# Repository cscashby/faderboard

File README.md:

# Fader Board (AKA Fraken-Mixer)

Multi-channel DAW control designed for portable wireless musical theatre use

## Problem statement

Normally musical theatre shows involve a fairly high number of radio microphones and a decent sized band/orchestra.  Generally in order to avoid feedback and other issues, the sound engineer needs to closely monitor / mix and quickly change faders during each scene to minimise the number of mics 'live' at any one time, and adjust for differences in the actors' voices and song dynamics.

In a traditional proscenium theatre this is fairly easy - a space is reserved at the back for the mix position, and the mixer and processing equipment (as well as the source for any SFX) is at the rear of the hall.

Enter promenade, or immersive, musical theatre - where the cast and audience are often in the same space, and the audience move through a number of rooms as the cast and the action takes them.

This is a very new genre of musical theatre, and hasn't really been done on a professional scale before - at least to my knowledge - and so when I was asked to do [Parade in Hemel Hempstead's Frogmore Paper Mill by Vivo D'Arte](http://www.vivodarte.co.uk/news.htm) - which required 20 radio microphones, a 7 piece orchestra, all in 5 different spaces, I apprehensively grasped at the challenge.

My approach at the time was to use a [Behringer Xtouch](https://www.musictri.be/Categories/Behringer/Computer-Audio/Desktop-Controllers/X-TOUCH/p/P0B1X) control surface, with a battery power unit and WiFi access client.  The result was good<sup>[1](#myfootnote1)</sup>, but it was a challenge because I only had 8 faders to use, couldn't change the 'page' or 'scene' myself, and couldn't trigger SFX or change speaker routing; I had a very capable team working with me who could do all of the above, so I managed, but it also was a very heavy box of tricks.

Another issue which arose over time was that the WiFi control was patchy - as the Xtouch isn't designed to be used with a spotty network connection, and being WiFi across a large space, the access client needed to disconnect and reconnect between multiple access points, disconnections were difficult - the Xtouch actually drops all the faders to -∞ so if you happen to touch them as it reconnects the channel dies unexpectedly. Not great.

So, what is required is a custom-built control surface which can control a number of channels of a mixing desk, without the constraints of a direct control solution like the Xtouch, and without the inherent problems with WiFi.

## Initial thoughts / concepts

### Scribble

Not very tidy, but hopefully this helps illustrate what's supposed to be happening.

### Tech decision

I went for an Arduino base for this project as I need embedded reliability and performance, without the overheads and inherent risks of using a SoC like the Raspberry Pi.  Given the complexity and number of I/O connections needed, I am basing the solution on an AT Mega 2560 - I got hold of [this dev board](http://amzn.to/2lO5UGc), but will probably design my own board from scratch for compactness

### Wireless comms

I need a long-range, full duplex transmit/receive solution for reasonably small payloads with a limited amount of overhead / latency.  I came across [LoRa](https://www.lora-alliance.org/) which seems to fit the bill, and I bought a couple of [dev boards for the RA-02 chip](http://amzn.to/2ELpx9M) which uses 433 MHz (or a couple of other free to use frequenceis).  I haven't completed testing yet but it seems to work well for my purposes.  What's more as it's designed for IoT, multiple receivers can be used to widen the transmit range if needed.

### Faders

Key to the solution is going to be the quality of fader units available, and they have to be motorised so they can be preset to values, and so that the sound #2s can also control if required.

Rather than evaluate a whole bunch of faders, I decided to buy [replacement faders for the Xtouch unit](https://www.gear4music.com/PA-DJ-and-Lighting/Behringer-X-Touch-Motor-Fader-MF100T-Set-of-5/1WME) instead - they are not that expensive, and I know them to be good.  They are 10 kΩ linear slide pots with a fast, accurate motor, and a touch sensitivity (capacitive touch) pin.

Touch sensitivity isn't something I've previously thought about, but this is a great option as it means that I can minimise my payload sent over the wire to only those faders which are being touched - making the device hopefully far more responsive.

### Scribble strips

Every good sound engineer deserves scribble strips (or something!) - they are invaluable for Musical Theatre - as each scene has different DCA assignments running, you can very quickly forget where you are as an operator.

I wanted multiple colours - as colour is a great way to distinguish between each channel.

I came across [these little OLED displays](https://thepihut.com/products/adafruit-monochrome-0-96-128x64-oled-graphic-display) which seem perfect as they're small, bright and easy to control via SPI.  I haven't yet received them so I'll update here as to how suitable they are.

Controlling lots of them isn't directly supported by their libraries so I'll need to do some custom coding to modify them for multiple units - multiplexing them through multiple CS pins.

### Everything else

I decided to duplicate the work I did in another project - '[pi-showcontrol'](github.com/cscashby/pi-showcontrol) and have a small TFT screen and programmable buttons in a 'master section' in the box - that way I can use SFX and have some feedback, possibly even plain text sent back to me by the Sound #2s which will hopefully be very useful.

### Power supply

This is probably the thing I've thought the least about.  I have a very reliable, high power battery which will give me any DC voltage I like and sensibly monitor time remaining, so I may stick with that for now; so a 5.5mm/2.5mm DC power jack may be all I need - probably 12v to minimise voltage regulator heating and run the whole thing at 5v.  However, if I feel brave later on I may well implement a battery control / charge unit.

### Physical manufacture

In my mind at present, I think the best approach is going to be to create a number of different PCBs:

1. Faders - in groups of 8 (so two identical boards).
2. Master control section - the TFT (although this may just be a module bolted to the case), buttons and big 'go' buttons).
3. Control board - the Arduino, radio chips and logic required to get the thing running.
4. Power supply - not sure what this will entail yet - watch this space.

I'd like to keep the unit as light as possible, but it will need sensible shielding (likely with pass-through capacitors for the 433 MHz antennae) - so I will be building the case out of sheet aluminium, probably cut using a CNC mill, or laser cut by a third party fabrication shop.  All of the controls will be mounted on the top panel, the control / power boards likely on the bottom panel, and the rear will be used for wired connections for charging, firmware upgrades and diagnostics.

On the sides of the box (which will likely need to be thicker / better reinforced) I will have holes for the straps which I will wear to use the unit whilst walking around (in [ice cream tray style](http://www.promotional-images.co.uk/ProdImages/2f9f440d-2c25-4093-97b0-d831b5edaa2b/classic2-lg.jpg) without the ice creams)

### The other end

Again this is early stages of the thought process, but a LoRa chip (probably the development board itself) with an ethernet HAT, which delivers an OSC payload to the mixing desk or a mac running [qLab](http://www.figure53.com/qlab).  Some form of queuing will be required so that if I end up with more than one of the receivers, then a controller will be required to marshal, deduplicate and send on this queue.

## Footnotes

<a name="myfootnote1">1</a>: 'No sitting at the back for him – [cscashby] he too followed the audience around with his sound desk in an usherette’s tray, ensuring that every cast member was heard, no matter what part of the building they were in.' [from Musical Theatre Review](http://musicaltheatrereview.com/parade-frogmore-paper-mill-hemel-hempstead/)

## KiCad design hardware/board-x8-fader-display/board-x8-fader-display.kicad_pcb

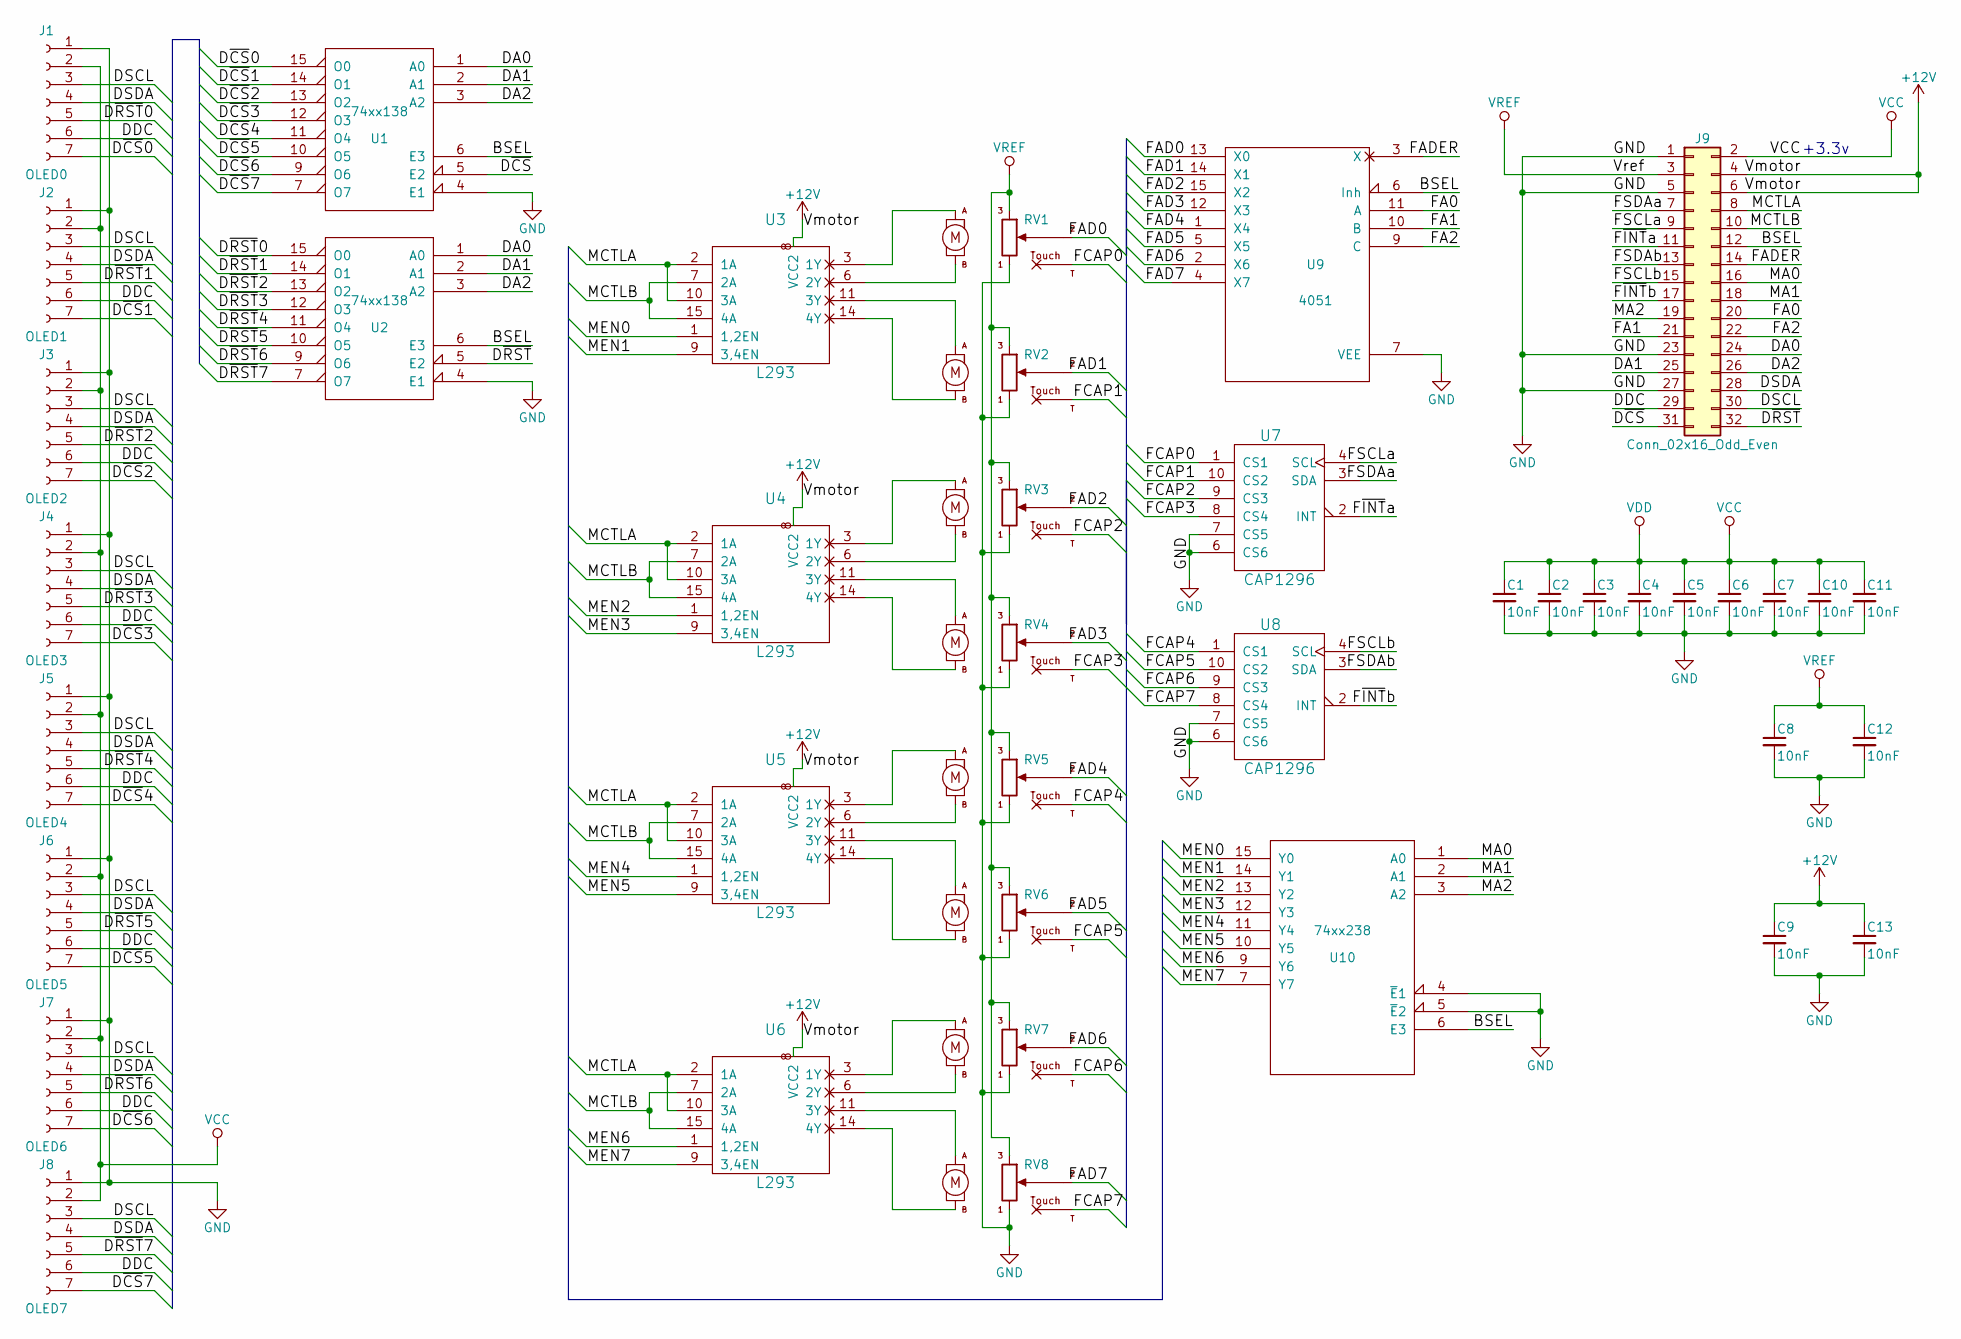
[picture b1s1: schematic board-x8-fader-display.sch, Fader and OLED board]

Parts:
C1, C2, C3, C4, C5, C6, C7, C8, C9, C10, C11, C12, C13: 10nF; C_Disc_D5.0mm_W2.5mm_P5.00mm
J1: OLED0; 0.95_SPI_SSD1306_Display
J2: OLED1; 0.95_SPI_SSD1306_Display
J3: OLED2; 0.95_SPI_SSD1306_Display
J4: OLED3; 0.95_SPI_SSD1306_Display
J5: OLED4; 0.95_SPI_SSD1306_Display
J6: OLED5; 0.95_SPI_SSD1306_Display
J7: OLED6; 0.95_SPI_SSD1306_Display
J8: OLED7; 0.95_SPI_SSD1306_Display
J9: Conn_02x16_Odd_Even; Pin_Header_Straight_2x16_Pitch2.54mm
RV1, RV2, RV3, RV4, RV5, RV6, RV7, RV8: RSA0N11M9A0J; AlpsFader_RSA0N11M9A0J
U1, U2: 74xx138; DIP-16_W7.62mm
U3, U4, U5, U6: L293; DIP-16_W7.62mm
U7, U8: CAP1296; DFN-10-1EP_3x3mm_Pitch0.5mm
U9: 4051; DIP-16_W7.62mm
U10: 74xx238; DIP-16_W7.62mm

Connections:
+12V: C9.1, C13.1, J9.4, J9.6, U3.8 (VCC2), U4.8 (VCC2), U5.8 (VCC2), U6.8 (VCC2)
/BSEL: J9.12, U1.6 (E3), U2.6 (E3), U9.6 (Inh), U10.6 (E3)
/DA0: J9.24, U1.1 (A0), U2.1 (A0)
/DA1: J9.25, U1.2 (A1), U2.2 (A1)
/DA2: J9.26, U1.3 (A2), U2.3 (A2)
/DDC: J1.6, J2.6, J3.6, J4.6, J5.6, J6.6, J7.6, J8.6, J9.29
/DSCL: J1.3, J2.3, J3.3, J4.3, J5.3, J6.3, J7.3, J8.3, J9.30
/DSDA: J1.4, J2.4, J3.4, J4.4, J5.4, J6.4, J7.4, J8.4, J9.28
/D~CS~: J9.31, U1.5 (E2)
/D~CS~0: J1.7, U1.15 (O0)
/D~CS~1: J2.7, U1.14 (O1)
/D~CS~2: J3.7, U1.13 (O2)
/D~CS~3: J4.7, U1.12 (O3)
/D~CS~4: J5.7, U1.11 (O4)
/D~CS~5: J6.7, U1.10 (O5)
/D~CS~6: J7.7, U1.9 (O6)
/D~CS~7: J8.7, U1.7 (O7)
/D~RST~: J9.32, U2.5 (E2)
/D~RST~0: J1.5, U2.15 (O0)
/D~RST~1: J2.5, U2.14 (O1)
/D~RST~2: J3.5, U2.13 (O2)
/D~RST~3: J4.5, U2.12 (O3)
/D~RST~4: J5.5, U2.11 (O4)
/D~RST~5: J6.5, U2.10 (O5)
/D~RST~6: J7.5, U2.9 (O6)
/D~RST~7: J8.5, U2.7 (O7)
/FA0: J9.20, U9.11 (A)
/FA1: J9.21, U9.10 (B)
/FA2: J9.22, U9.9 (C)
/FAD0: RV1.2, U9.13 (X0)
/FAD1: RV2.2, U9.14 (X1)
/FAD2: RV3.2, U9.15 (X2)
/FAD3: RV4.2, U9.12 (X3)
/FAD4: RV5.2, U9.1 (X4)
/FAD5: RV6.2, U9.5 (X5)
/FAD6: RV7.2, U9.2 (X6)
/FAD7: RV8.2, U9.4 (X7)
/FADER: J9.14, U9.3 (X)
/FCAP0: RV1.T (Touch), U7.1 (CS1)
/FCAP1: RV2.T (Touch), U7.10 (CS2)
/FCAP2: RV3.T (Touch), U7.9 (CS3)
/FCAP3: RV4.T (Touch), U7.8 (CS4)
/FCAP4: RV5.T (Touch), U8.1 (CS1)
/FCAP5: RV6.T (Touch), U8.10 (CS2)
/FCAP6: RV7.T (Touch), U8.9 (CS3)
/FCAP7: RV8.T (Touch), U8.8 (CS4)
/FSCLa: J9.9, U7.4 (SCL)
/FSCLb: J9.15, U8.4 (SCL)
/FSDAa: J9.7, U7.3 (SDA)
/FSDAb: J9.13, U8.3 (SDA)
/F~INT~a: J9.11, U7.2 (INT)
/F~INT~b: J9.17, U8.2 (INT)
/MA0: J9.16, U10.1 (A0)
/MA1: J9.18, U10.2 (A1)
/MA2: J9.19, U10.3 (A2)
/MCTLA: J9.8, U3.2 (1A), U3.10 (3A), U4.2 (1A), U4.10 (3A), U5.2 (1A), U5.10 (3A), U6.2 (1A), U6.10 (3A)
/MCTLB: J9.10, U3.7 (2A), U3.15 (4A), U4.7 (2A), U4.15 (4A), U5.7 (2A), U5.15 (4A), U6.7 (2A), U6.15 (4A)
/MEN0: U3.1 (1,2EN), U10.15 (Y0)
/MEN1: U3.9 (3,4EN), U10.14 (Y1)
/MEN2: U4.1 (1,2EN), U10.13 (Y2)
/MEN3: U4.9 (3,4EN), U10.12 (Y3)
/MEN4: U5.1 (1,2EN), U10.11 (Y4)
/MEN5: U5.9 (3,4EN), U10.10 (Y5)
/MEN6: U6.1 (1,2EN), U10.9 (Y6)
/MEN7: U6.9 (3,4EN), U10.7 (Y7)
GND: C1.2, C2.2, C3.2, C4.2, C5.2, C6.2, C7.2, C8.2, C9.2, C10.2, C11.2, C12.2, C13.2, J1.1, J2.1, J3.1, J4.1, J5.1, J6.1, J7.1, J8.1, J9.1, J9.5, J9.23, J9.27, RV1.3, RV2.3, RV3.3, RV4.3, RV5.3, RV6.3, RV7.3, RV8.3, U1.4 (E1), U1.8 (GND), U2.4 (E1), U2.8 (GND), U3.4 (GND), U3.5 (GND), U3.12 (GND), U3.13 (GND), U4.4 (GND), U4.5 (GND), U4.12 (GND), U4.13 (GND), U5.4 (GND), U5.5 (GND), U5.12 (GND), U5.13 (GND), U6.4 (GND), U6.5 (GND), U6.12 (GND), U6.13 (GND), U7.6 (CS6), U7.7 (CS5), U7.11 (GND), U8.6 (CS6), U8.7 (CS5), U8.11 (GND), U9.7 (VEE), U9.8 (GND), U10.4 (~E~1), U10.5 (~E~2), U10.8 (GND)
unnamed: RV1.A, U3.3 (1Y)
unnamed: RV1.B, U3.6 (2Y)
unnamed: RV2.A, U3.11 (3Y)
unnamed: RV2.B, U3.14 (4Y)
unnamed: RV3.A, U4.3 (1Y)
unnamed: RV3.B, U4.6 (2Y)
unnamed: RV4.A, U4.11 (3Y)
unnamed: RV4.B, U4.14 (4Y)
unnamed: RV5.A, U5.3 (1Y)
unnamed: RV5.B, U5.6 (2Y)
unnamed: RV6.A, U5.11 (3Y)
unnamed: RV6.B, U5.14 (4Y)
unnamed: RV7.A, U6.3 (1Y)
unnamed: RV7.B, U6.6 (2Y)
unnamed: RV8.A, U6.11 (3Y)
unnamed: RV8.B, U6.14 (4Y)
VCC: C1.1, C2.1, C3.1, C4.1, C5.1, C6.1, C7.1, C10.1, C11.1, J1.2, J2.2, J3.2, J4.2, J5.2, J6.2, J7.2, J8.2, J9.2, U1.16 (VCC), U2.16 (VCC), U3.16 (VCC), U4.16 (VCC), U5.16 (VCC), U6.16 (VCC), U7.5 (VDD), U8.5 (VDD), U9.16 (VCC), U10.16 (VCC)
VREF: C8.1, C12.1, J9.3, RV1.1, RV2.1, RV3.1, RV4.1, RV5.1, RV6.1, RV7.1, RV8.1

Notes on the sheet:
+3.3v

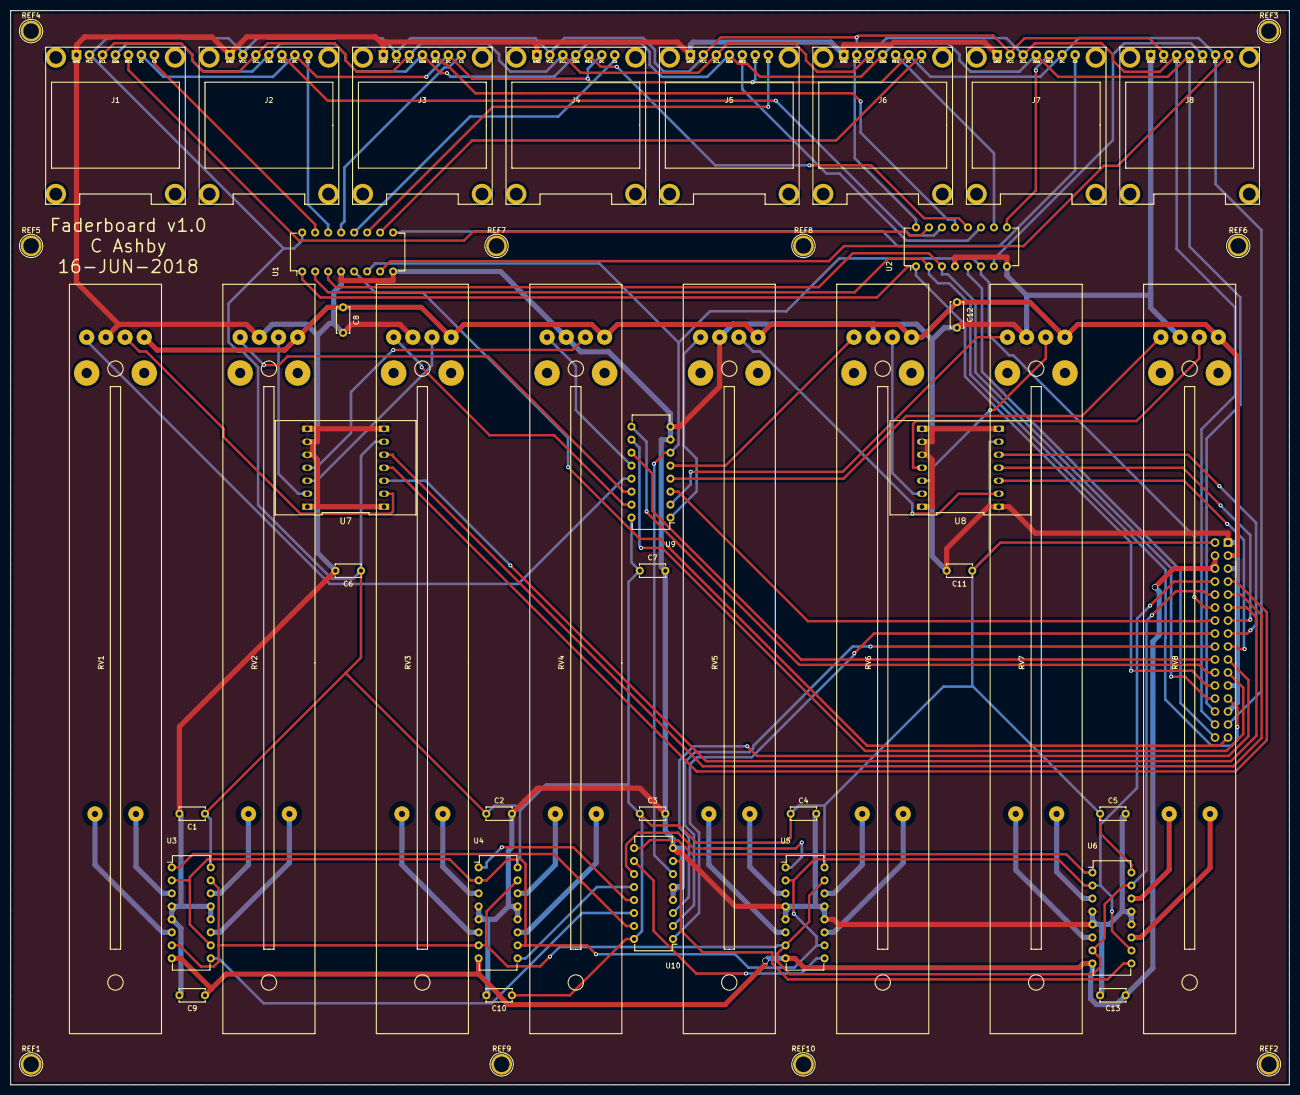
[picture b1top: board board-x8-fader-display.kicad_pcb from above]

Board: 2 copper layers, 250.0 x 210.0 mm, 50 parts (1 on the bottom side), 84 nets.

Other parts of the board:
REF1, REF2, REF3, REF4, REF5, REF6, REF7, REF8, REF9, REF10: 1pin

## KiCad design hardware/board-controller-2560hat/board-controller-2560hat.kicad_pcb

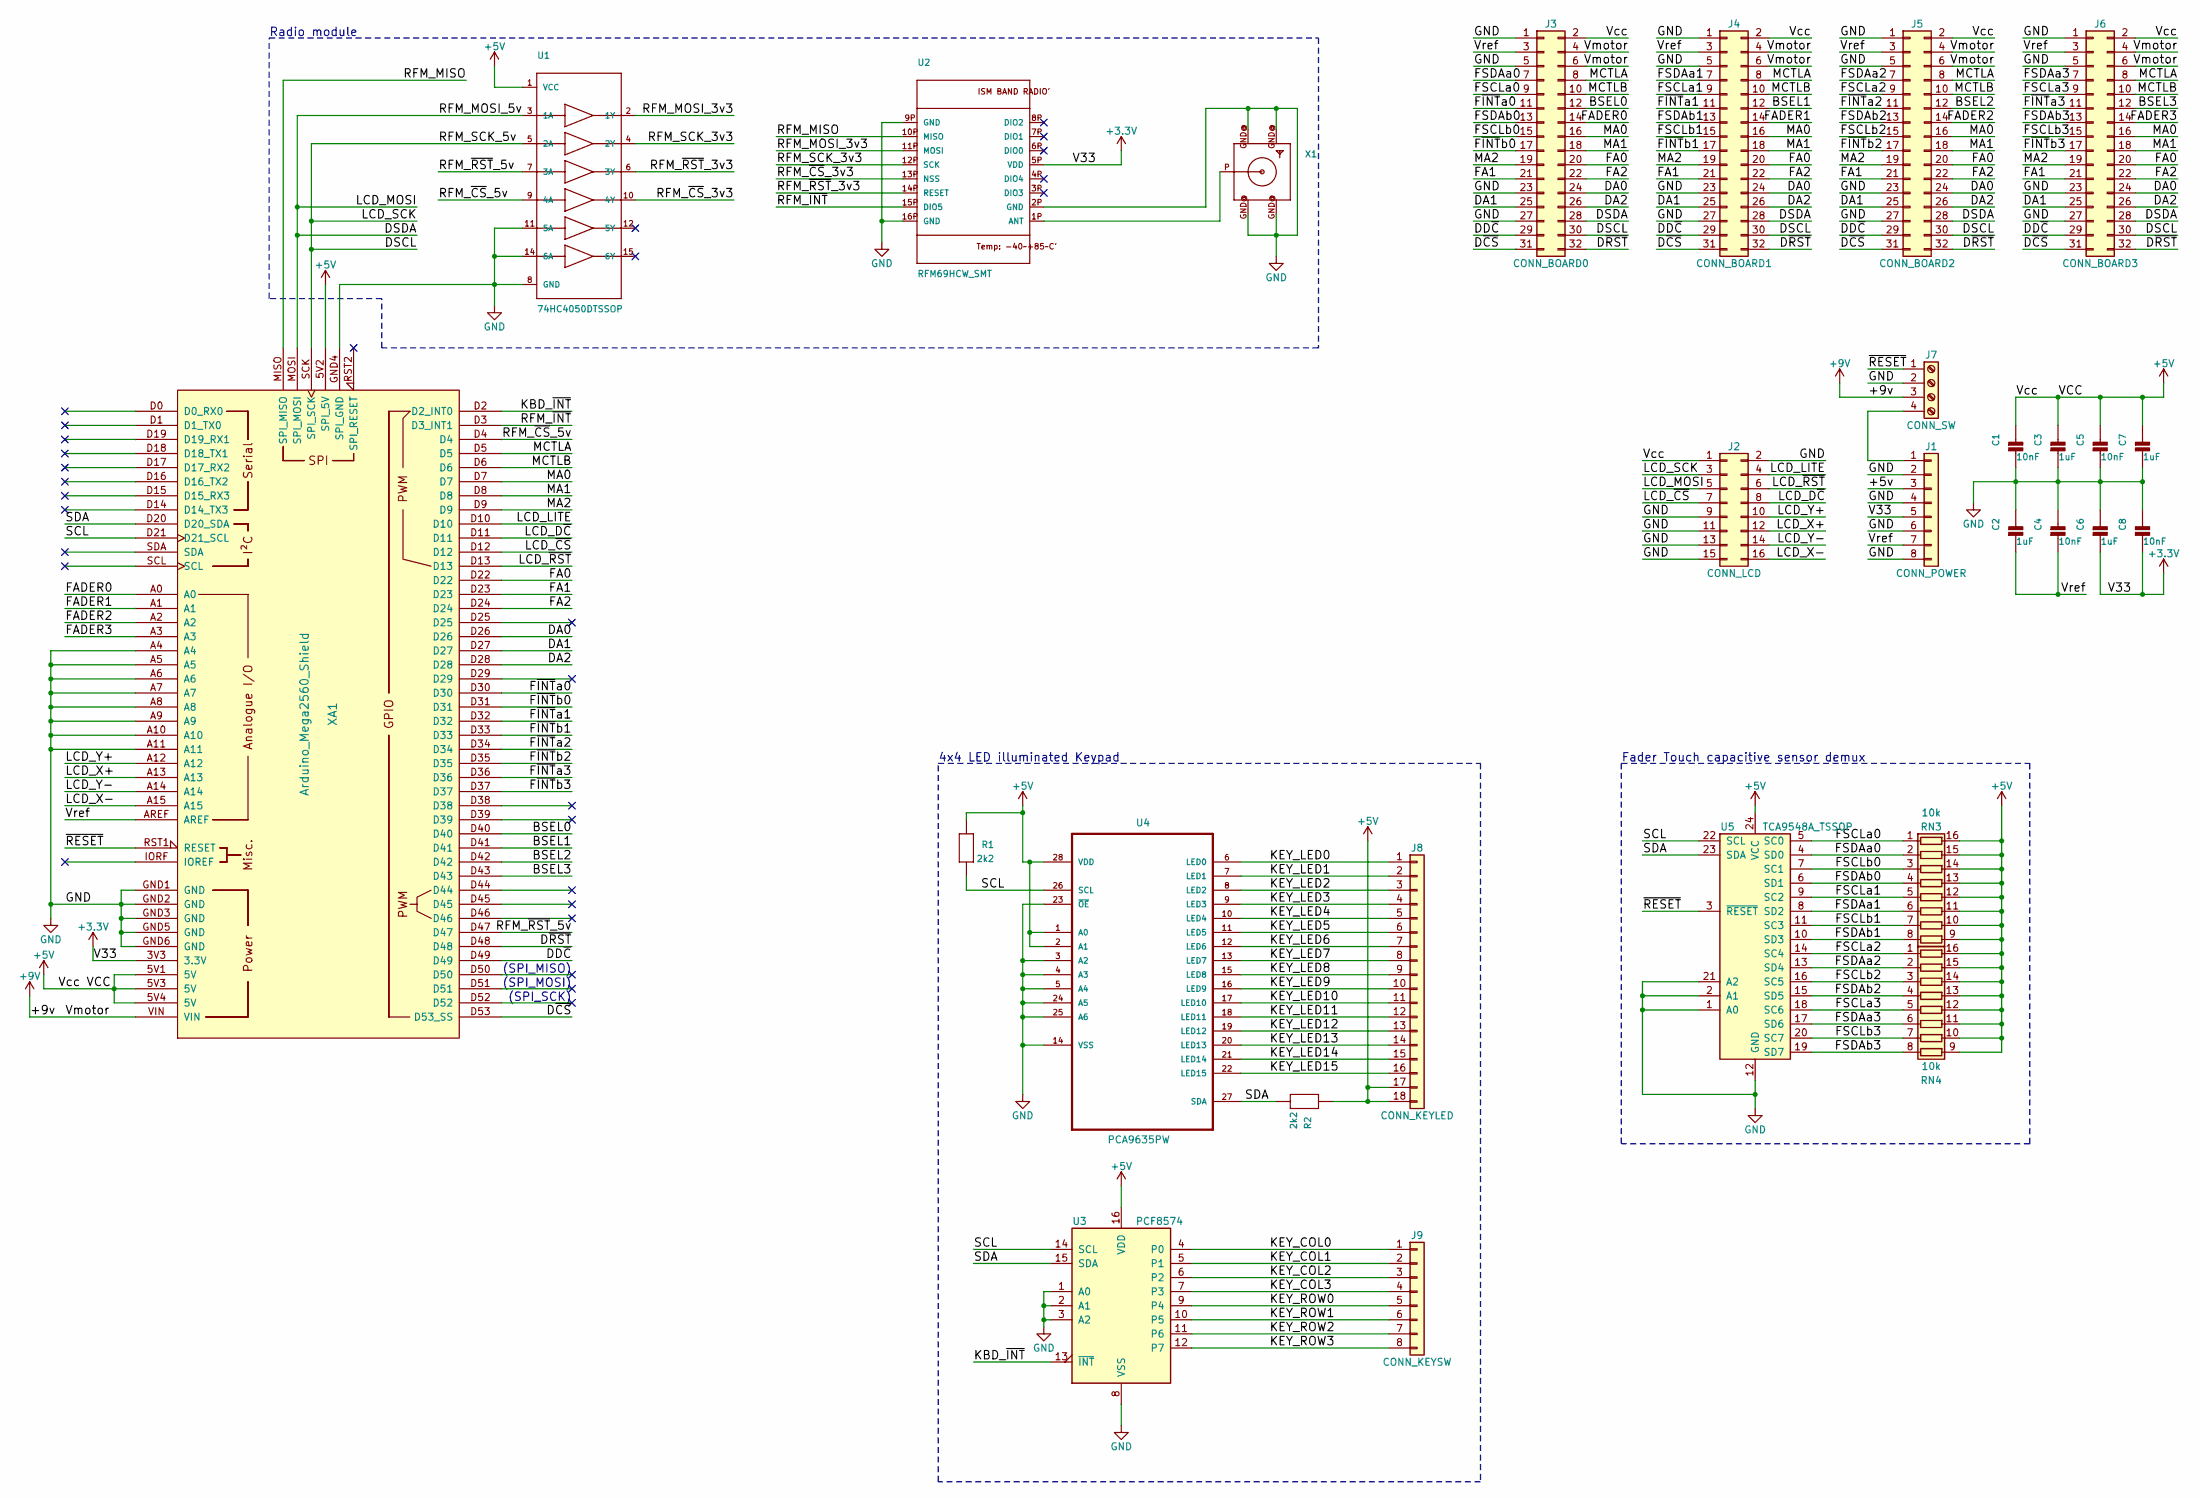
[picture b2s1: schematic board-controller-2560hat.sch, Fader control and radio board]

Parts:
C1, C4, C5, C8: 10nF; C_0603_HandSoldering
C2, C3, C6, C7: 1uF; C_0603_HandSoldering
J1: CONN_POWER; Pin_Header_Straight_1x08_Pitch2.54mm
J2: CONN_LCD; Pin_Header_Straight_2x08_Pitch2.54mm
J3: CONN_BOARD0; Pin_Header_Straight_2x16_Pitch2.54mm
J4: CONN_BOARD1; Pin_Header_Straight_2x16_Pitch2.54mm
J5: CONN_BOARD2; Pin_Header_Straight_2x16_Pitch2.54mm
J6: CONN_BOARD3; Pin_Header_Straight_2x16_Pitch2.54mm
J7: CONN_SW; TerminalBlock_Pheonix_MPT-2.54mm_4pol
J8: CONN_KEYLED; Pin_Header_Straight_1x18_Pitch2.54mm
J9: CONN_KEYSW; Pin_Header_Straight_1x08_Pitch2.54mm
R1, R2: 2k2; C_1206_HandSoldering
RN3, RN4: 10k; CA_SOIC_16_5.59x11.18_1.27_Pitch
U1: 74HC4050DTSSOP; SSOP-16_5.3x6.2mm_Pitch0.65mm
U2: RFM69HCW_SMT; RFMHCW_SMT
U3: PCF8574; CA_SOIC_16_7.5x10.5_1.27_Pitch
U4: PCA9635PW; TSSOP-28_4.4x9.7mm_Pitch0.65mm
U5: TCA9548A_TSSOP; TSSOP-24_4.4x7.8mm_Pitch0.65mm
X1: SMACONNECTOR_EDGE; SMA_EDGELAUNCH
XA1: Arduino_Mega2560_Shield

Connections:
+3V3: C6.2, C8.2, J1.5, U2.5P (VDD), XA1.3V3 (3.3V)
+5V: C1.1, C3.1, C5.1, C7.1, J1.3, J2.1, J3.2, J4.2, J5.2, J6.2, J8.17, J8.18, R1.2, R2.2, RN3.9 (R8.2), RN3.10 (R7.2), RN3.11 (R6.2), RN3.12 (R5.2), RN3.13 (R4.2), RN3.14 (R3.2), RN3.15 (R2.2), RN3.16 (R1.2), RN4.9 (R8.2), RN4.10 (R7.2), RN4.11 (R6.2), RN4.12 (R5.2), RN4.13 (R4.2), RN4.14 (R3.2), RN4.15 (R2.2), RN4.16 (R1.2), U1.1 (VCC), U3.16 (VDD), U4.1 (A0), U4.2 (A1), U4.28 (VDD), U5.24 (VCC), XA1.5V1 (5V), XA1.5V2 (SPI_5V), XA1.5V3 (5V), XA1.5V4 (5V)
+9V: J3.4, J3.6, J4.4, J4.6, J5.4, J5.6, J6.4, J6.6, J7.3, XA1.VIN
/BSEL0: J3.12, XA1.D40
/BSEL1: J4.12, XA1.D41
/BSEL2: J5.12, XA1.D42
/BSEL3: J6.12, XA1.D43
/DA0: J3.24, J4.24, J5.24, J6.24, XA1.D26
/DA1: J3.25, J4.25, J5.25, J6.25, XA1.D27
/DA2: J3.26, J4.26, J5.26, J6.26, XA1.D28
/DD~C~: J3.29, J4.29, J5.29, J6.29, XA1.D49
/DSCL: J2.3, J3.30, J4.30, J5.30, J6.30, U1.5 (2A), XA1.SCK (SPI_SCK)
/DSDA: J2.5, J3.28, J4.28, J5.28, J6.28, U1.3 (1A), XA1.MOSI (SPI_MOSI)
/D~CS~: J3.31, J4.31, J5.31, J6.31, XA1.D53 (D53_SS)
/D~RST~: J3.32, J4.32, J5.32, J6.32, XA1.D48
/FA0: J3.20, J4.20, J5.20, J6.20, XA1.D22
/FA1: J3.21, J4.21, J5.21, J6.21, XA1.D23
/FA2: J3.22, J4.22, J5.22, J6.22, XA1.D24
/FADER0: J3.14, XA1.A0
/FADER1: J4.14, XA1.A1
/FADER2: J5.14, XA1.A2
/FADER3: J6.14, XA1.A3
/FSCLa0: J3.9, RN3.1 (R1.1), U5.5 (SC0)
/FSCLa1: J4.9, RN3.5 (R5.1), U5.9 (SC2)
/FSCLa2: J5.9, RN4.1 (R1.1), U5.14 (SC4)
/FSCLa3: J6.9, RN4.5 (R5.1), U5.18 (SC6)
/FSCLb0: J3.15, RN3.3 (R3.1), U5.7 (SC1)
/FSCLb1: J4.15, RN3.7 (R7.1), U5.11 (SC3)
/FSCLb2: J5.15, RN4.3 (R3.1), U5.16 (SC5)
/FSCLb3: J6.15, RN4.7 (R7.1), U5.20 (SC7)
/FSDAa0: J3.7, RN3.2 (R2.1), U5.4 (SD0)
/FSDAa1: J4.7, RN3.6 (R6.1), U5.8 (SD2)
/FSDAa2: J5.7, RN4.2 (R2.1), U5.13 (SD4)
/FSDAa3: J6.7, RN4.6 (R6.1), U5.17 (SD6)
/FSDAb0: J3.13, RN3.4 (R4.1), U5.6 (SD1)
/FSDAb1: J4.13, RN3.8 (R8.1), U5.10 (SD3)
/FSDAb2: J5.13, RN4.4 (R4.1), U5.15 (SD5)
/FSDAb3: J6.13, RN4.8 (R8.1), U5.19 (SD7)
/F~INT~a0: J3.11, XA1.D30
/F~INT~a1: J4.11, XA1.D32
/F~INT~a2: J5.11, XA1.D34
/F~INT~a3: J6.11, XA1.D36
/F~INT~b0: J3.17, XA1.D31
/F~INT~b1: J4.17, XA1.D33
/F~INT~b2: J5.17, XA1.D35
/F~INT~b3: J6.17, XA1.D37
/KBD_~INT~: U3.13 (~INT~), XA1.D2 (D2_INT0)
/KEY_COL0: J9.1, U3.4 (P0)
/KEY_COL1: J9.2, U3.5 (P1)
/KEY_COL2: J9.3, U3.6 (P2)
/KEY_COL3: J9.4, U3.7 (P3)
/KEY_LED0: J8.1, U4.6 (LED0)
/KEY_LED1: J8.2, U4.7 (LED1)
/KEY_LED2: J8.3, U4.8 (LED2)
/KEY_LED3: J8.4, U4.9 (LED3)
/KEY_LED4: J8.5, U4.10 (LED4)
/KEY_LED5: J8.6, U4.11 (LED5)
/KEY_LED6: J8.7, U4.12 (LED6)
/KEY_LED7: J8.8, U4.13 (LED7)
/KEY_LED8: J8.9, U4.15 (LED8)
/KEY_LED9: J8.10, U4.16 (LED9)
/KEY_LED10: J8.11, U4.17 (LED10)
/KEY_LED11: J8.12, U4.18 (LED11)
/KEY_LED12: J8.13, U4.19 (LED12)
/KEY_LED13: J8.14, U4.20 (LED13)
/KEY_LED14: J8.15, U4.21 (LED14)
/KEY_LED15: J8.16, U4.22 (LED15)
/KEY_ROW0: J9.5, U3.9 (P4)
/KEY_ROW1: J9.6, U3.10 (P5)
/KEY_ROW2: J9.7, U3.11 (P6)
/KEY_ROW3: J9.8, U3.12 (P7)
/LCD_D~C~: J2.8, XA1.D11
/LCD_LITE: J2.4, XA1.D10
/LCD_X+: J2.12, XA1.A13
/LCD_X-: J2.16, XA1.A15
/LCD_Y+: J2.10, XA1.A12
/LCD_Y-: J2.14, XA1.A14
/LCD_~CS~: J2.7, XA1.D12
/LCD_~RST~: J2.6, XA1.D13
/MA0: J3.16, J4.16, J5.16, J6.16, XA1.D7
/MA1: J3.18, J4.18, J5.18, J6.18, XA1.D8
/MA2: J3.19, J4.19, J5.19, J6.19, XA1.D9
/MCTLA: J3.8, J4.8, J5.8, J6.8, XA1.D5
/MCTLB: J3.10, J4.10, J5.10, J6.10, XA1.D6
/RFM_MISO: U2.10P (MISO), XA1.MISO (SPI_MISO)
/RFM_MOSI_3v3: U1.2 (1Y), U2.11P (MOSI)
/RFM_SCK_3v3: U1.4 (2Y), U2.12P (SCK)
/RFM_~CS~_3v3: U1.10 (4Y), U2.13P (NSS)
/RFM_~CS~_5v: U1.9 (4A), XA1.D4
/RFM_~INT~: U2.15P (DIO5), XA1.D3 (D3_INT1)
/RFM_~RST~_3v3: U1.6 (3Y), U2.14P (RESET)
/RFM_~RST~_5v: U1.7 (3A), XA1.D47
/SCL: R1.1, U3.14 (SCL), U4.26 (SCL), U5.22 (SCL), XA1.D21 (D21_SCL)
/SDA: R2.1, U3.15 (SDA), U4.27 (SDA), U5.23 (SDA), XA1.D20 (D20_SDA)
/Vref: C2.2, C4.2, J1.7, J3.3, J4.3, J5.3, J6.3, XA1.AREF
/~RESET~: J7.1, U5.3 (~RESET), XA1.RST1 (RESET)
GND: C1.2, C2.1, C3.2, C4.1, C5.2, C6.1, C7.2, C8.1, J1.2, J1.4, J1.6, J1.8, J2.2, J2.9, J2.11, J2.13, J2.15, J3.1, J3.5, J3.23, J3.27, J4.1, J4.5, J4.23, J4.27, J5.1, J5.5, J5.23, J5.27, J6.1, J6.5, J6.23, J6.27, J7.2, U1.8 (GND), U1.11 (5A), U1.14 (6A), U2.2P (GND), U2.9P (GND), U2.16P (GND), U3.1 (A0), U3.2 (A1), U3.3 (A2), U3.8 (VSS), U4.3 (A2), U4.4 (A3), U4.5 (A4), U4.14 (VSS), U4.23 (~OE), U4.24 (A5), U4.25 (A6), U5.1 (A0), U5.2 (A1), U5.12 (GND), U5.21 (A2), X1.GND@ (GND1), XA1.A4, XA1.A5, XA1.A6, XA1.A7, XA1.A8, XA1.A9, XA1.A10, XA1.A11, XA1.GND1 (GND), XA1.GND2 (GND), XA1.GND3 (GND), XA1.GND4 (SPI_GND), XA1.GND5 (GND), XA1.GND6 (GND)
unnamed: J1.1, J7.4
unnamed: U2.1P (ANT), X1.P (ANT)

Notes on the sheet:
Fader Touch capacitive sensor demux
Radio module
4x4 LED illuminated Keypad
(SPI_MOSI)
(SPI_MISO)
(SPI_SCK)

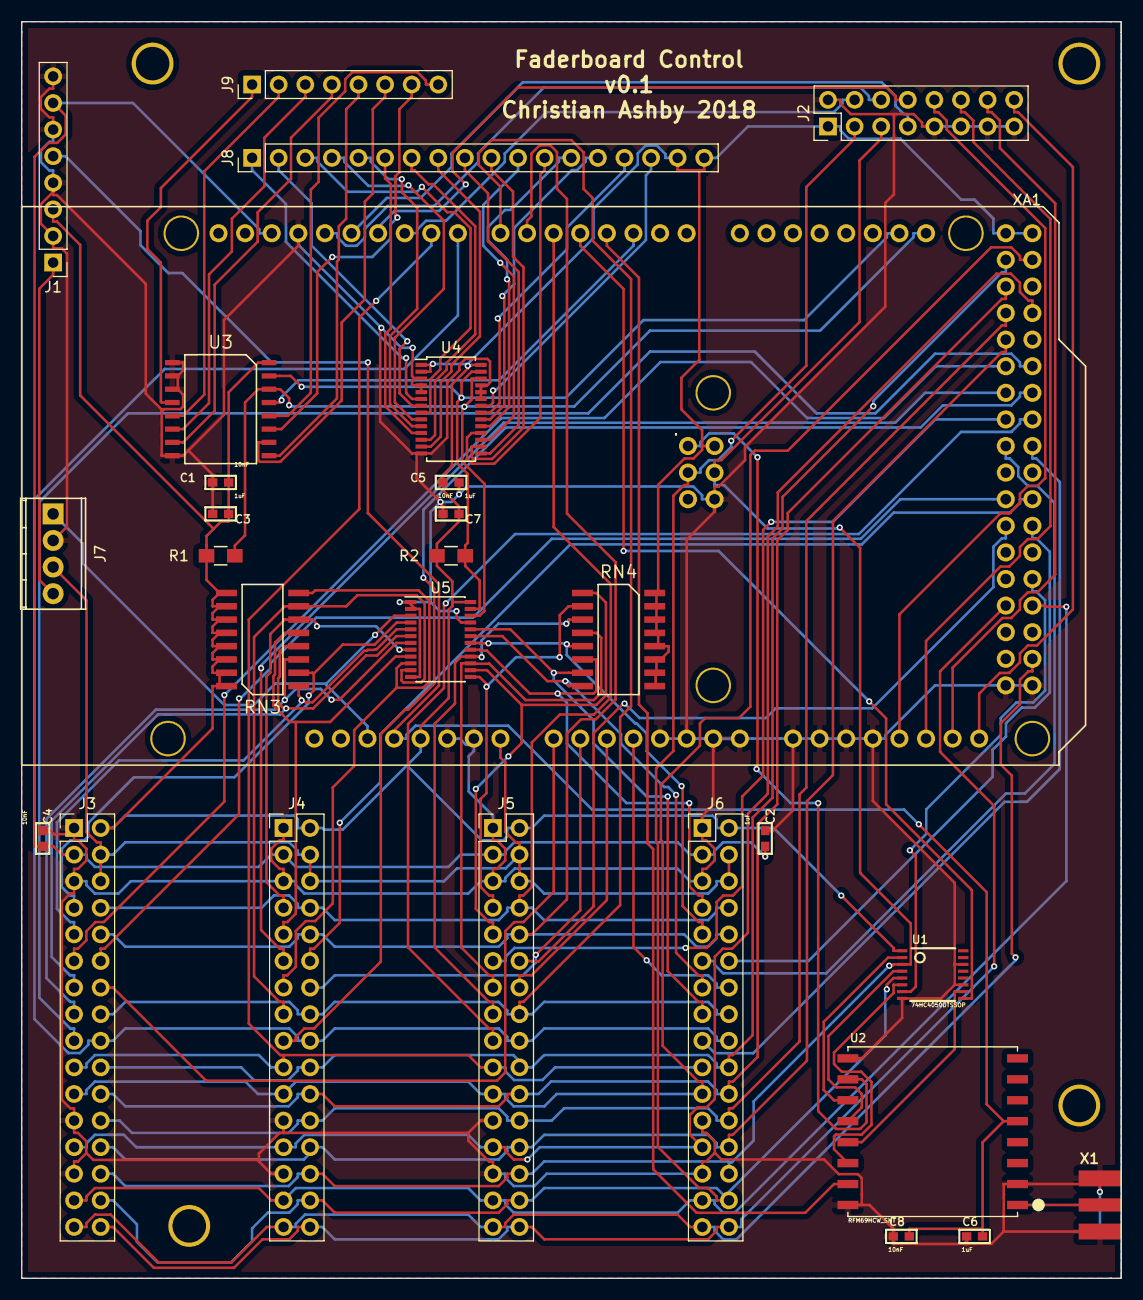
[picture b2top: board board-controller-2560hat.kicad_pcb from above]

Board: 2 copper layers, 105.0 x 120.0 mm, 28 parts (0 on the bottom side), 99 nets.

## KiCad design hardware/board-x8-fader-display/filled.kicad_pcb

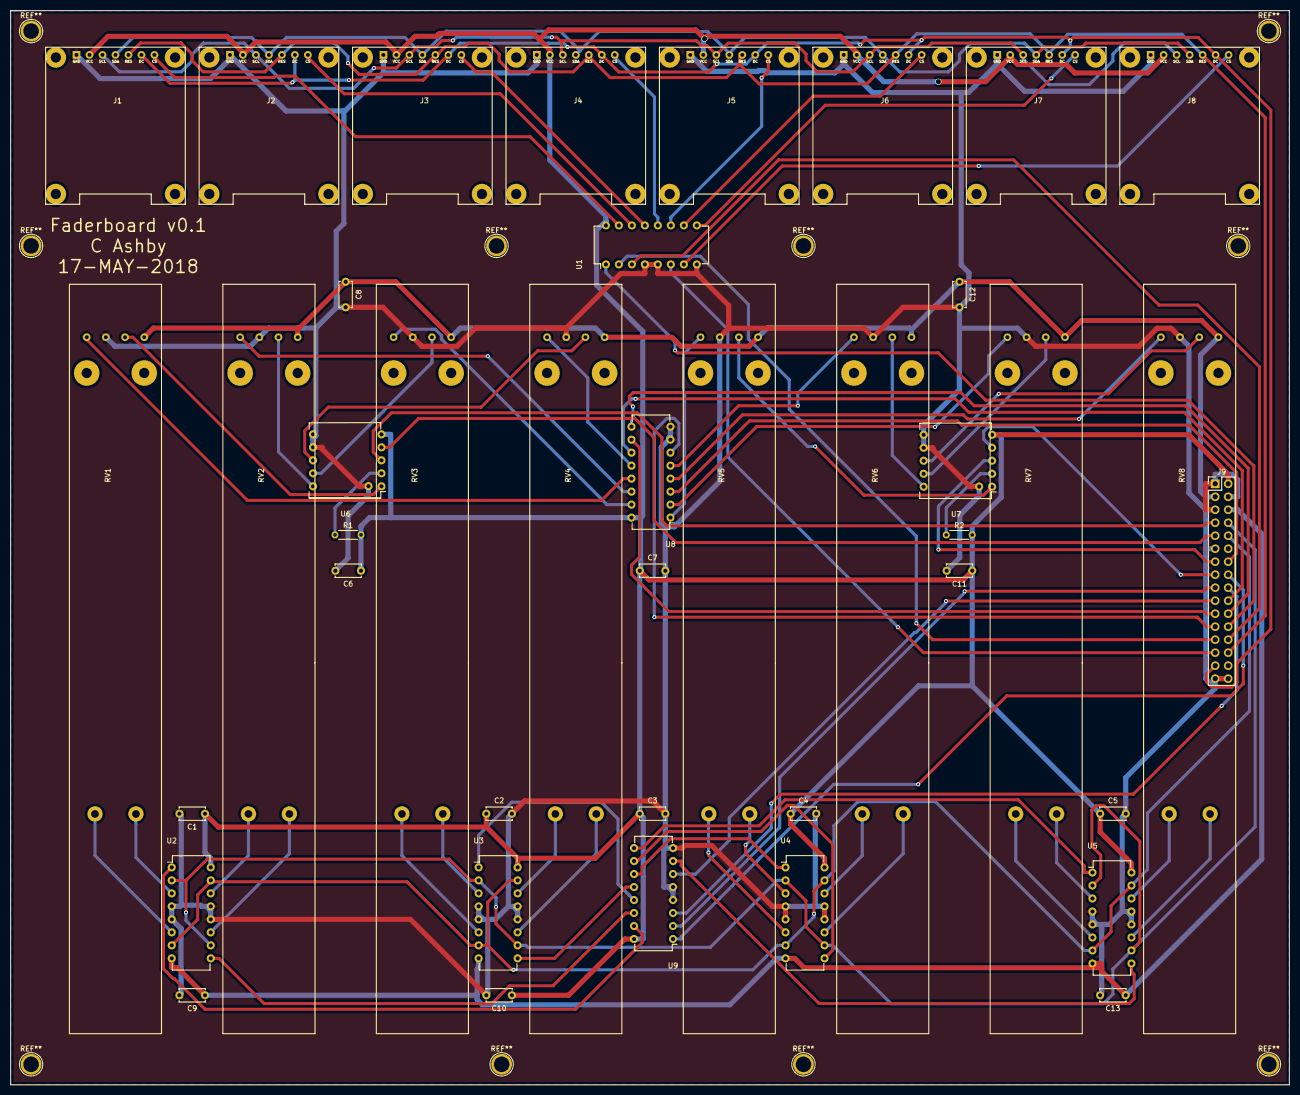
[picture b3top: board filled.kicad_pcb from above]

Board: 2 copper layers, 250.0 x 210.0 mm, 41 parts (0 on the bottom side), 77 nets.

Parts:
C1, C2, C3, C4, C5, C6, C7, C8, C9, C10, C11, C12, C13: 10nF; C_Disc_D5.0mm_W2.5mm_P5.00mm
J1: OLED0; 0.95_SPI_SSD1306_Display
J2: OLED1; 0.95_SPI_SSD1306_Display
J3: OLED2; 0.95_SPI_SSD1306_Display
J4: OLED3; 0.95_SPI_SSD1306_Display
J5: OLED4; 0.95_SPI_SSD1306_Display
J6: OLED5; 0.95_SPI_SSD1306_Display
J7: OLED6; 0.95_SPI_SSD1306_Display
J8: OLED7; 0.95_SPI_SSD1306_Display
J9: Conn_02x16_Odd_Even; Pin_Header_Straight_2x16_Pitch2.54mm
R1, R2: 2k2; R_Axial_DIN0204_L3.6mm_D1.6mm_P5.08mm_Horizontal
RV1, RV2, RV3, RV4, RV5, RV6, RV7, RV8: RSA0N11M9A0J; AlpsFader_RSA0N11M9A0J
U1, U9: 74xx238; DIP-16_W7.62mm
U2, U3, U4, U5: L293; DIP-16_W7.62mm
U6, U7: CAP1296; DIP-10_W13.38mm+GND
U8: 4051; DIP-16_W7.62mm

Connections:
+12V: C9.1, C13.1, J9.6, U2.8, U3.8, U4.8, U5.8
/DA0: J9.24, U1.1
/DA1: J9.25, U1.2
/DA2: J9.26, U1.3
/DA3: J9.27, U1.6
/DCS0: J1.7, U1.15
/DCS1: J2.7, U1.14
/DCS2: J3.7, U1.13
/DCS3: J4.7, U1.12
/DCS4: J5.7, U1.11
/DCS5: J6.7, U1.10
/DCS6: J7.7, U1.9
/DCS7: J8.7, U1.7
/DDC: J1.6, J2.6, J3.6, J4.6, J5.6, J6.6, J7.6, J8.6, J9.29
/D~RST~: J1.5, J2.5, J3.5, J4.5, J5.5, J6.5, J7.5, J8.5, J9.28
/FA0: J9.20, U8.11
/FA1: J9.21, U8.10
/FA2: J9.22, U8.9
/FA3: J9.23, U8.6
/FAD0: RV1.2, U8.13
/FAD1: RV2.2, U8.14
/FAD2: RV3.2, U8.15
/FAD3: RV4.2, U8.12
/FAD4: RV5.2, U8.1
/FAD5: RV6.2, U8.5
/FAD6: RV7.2, U8.2
/FAD7: RV8.2, U8.4
/FADER: J9.14, U8.3
/FCAP0: RV1.T, U6.1
/FCAP1: RV2.T, U6.10
/FCAP2: RV3.T, U6.9
/FCAP3: RV4.T, U6.8
/FCAP4: RV5.T, U7.1
/FCAP5: RV6.T, U7.10
/FCAP6: RV7.T, U7.9
/FCAP7: RV8.T, U7.8
/FSCL: J1.3, J2.3, J3.3, J4.3, J5.3, J6.3, J7.3, J8.3
/FSCLa: J9.9, U6.4
/FSCLb: J9.15, U7.4
/FSDA: J1.4, J2.4, J3.4, J4.4, J5.4, J6.4, J7.4, J8.4
/FSDAa: J9.7, U6.3
/FSDAb: J9.13, U7.3
/MA0: J9.16, U9.1
/MA1: J9.17, U9.2
/MA2: J9.18, U9.3
/MA3: J9.19, U9.6
/MCTLA: J9.8, U2.2, U2.10, U3.2, U3.10, U4.2, U4.10, U5.2, U5.10
/MCTLB: J9.10, U2.7, U2.15, U3.7, U3.15, U4.7, U4.15, U5.7, U5.15
/MEN0: U2.1, U9.15
/MEN1: U2.9, U9.14
/MEN2: U3.1, U9.13
/MEN3: U3.9, U9.12
/MEN4: U4.1, U9.11
/MEN5: U4.9, U9.10
/MEN6: U5.1, U9.9
/MEN7: U5.9, U9.7
GND: C1.2, C2.2, C3.2, C4.2, C5.2, C6.2, C7.2, C8.2, C9.2, C10.2, C11.2, C12.2, C13.2, J1.1, J2.1, J3.1, J4.1, J5.1, J6.1, J7.1, J8.1, J9.1, J9.4, J9.5, J9.11, J9.31, J9.32, RV1.3, RV2.3, RV3.3, RV4.3, RV5.3, RV6.3, RV7.3, RV8.3, U1.4, U1.5, U1.8, U2.4, U2.5, U2.12, U2.13, U3.4, U3.5, U3.12, U3.13, U4.4, U4.5, U4.12, U4.13, U5.4, U5.5, U5.12, U5.13, U6.6, U6.7, U6.11, U7.6, U7.7, U7.11, U8.7, U8.8, U9.4, U9.5, U9.8
unnamed: R1.1, U6.2
unnamed: R2.1, U7.2
unnamed: RV1.A, U2.3
unnamed: RV1.B, U2.6
unnamed: RV2.A, U2.11
unnamed: RV2.B, U2.14
unnamed: RV3.A, U3.3
unnamed: RV3.B, U3.6
unnamed: RV4.A, U3.11
unnamed: RV4.B, U3.14
unnamed: RV5.A, U4.3
unnamed: RV5.B, U4.6
unnamed: RV6.A, U4.11
unnamed: RV6.B, U4.14
unnamed: RV7.A, U5.3
unnamed: RV7.B, U5.6
unnamed: RV8.A, U5.11
unnamed: RV8.B, U5.14
VCC: C1.1, C2.1, C3.1, C4.1, C5.1, C6.1, C7.1, C10.1, C11.1, J1.2, J2.2, J3.2, J4.2, J5.2, J6.2, J7.2, J8.2, J9.2, R1.2, R2.2, U1.16, U2.16, U3.16, U4.16, U5.16, U6.5, U7.5, U8.16, U9.16
VREF: C8.1, C12.1, J9.3, RV1.1, RV2.1, RV3.1, RV4.1, RV5.1, RV6.1, RV7.1, RV8.1

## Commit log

2018-01-03 First add - version for faders only (no buttons) and wrong headers
2018-01-03 Adding scribbled picture for docs
2018-01-03 Crop image
2018-01-03 First real docs
    Lots of blurb about the project.
2018-01-03 Fixed format, more commentary
2018-01-03 Format fix
2018-01-03 Words, fixing the words.
    Typo fix.
2018-01-03 PDF schematic (WIP like everything else)
2018-01-03 Removed wrong headers, fixed V33 vs VCC mapping
2018-01-12 Added useful docs
2018-01-27 Pre-tidy folder structure
2018-01-27 Adding SSD_13XX module
2018-01-27 Adding libraries and POC test files
2018-01-27 Cleaning up old schematics
2018-01-27 Added fader details and schematic file
2018-01-27 Table in markdown fix
2018-01-27 First cut at fader schema, new libraries and consistent power naming
2018-01-27 Added gitignore for KiCAD
2018-01-27 Removing backups
2018-01-27 Adding L293 lib, moving motor to sensible place in fader lib
2018-01-27 Fader board schematic updates
2018-01-28 adding more wires to schematic, still need board connectors
2018-01-28 Adding board connection summary
2018-01-28 Added board connections (first pass)
    See https://goo.gl/jBwiur for source (use sheets to markdown add-on)
2018-01-28 Fix heading
2018-01-28 No OLED support yet - Need to make this clear
2018-01-28 Added connector layout
2018-01-28 Updated for OLED
2018-01-28 Completed faders and OLED, some bugs with power pins
2018-01-28 Fixing schema issues
2018-01-28 Replaced MPR121 with CAP1296 due to 3.3v limitation - added multiplexed I2C for CAP1296
2018-01-28 Updated connections for CAP1296 change
2018-01-28 Adding board schematic first revision
2018-01-28 Minor update with note to check I2C pullups
2018-02-16 Adding Fader data sheet, Schema v1 for faders complete, starting to get footprints sorted out
2018-02-18 Added LCD footprint and supporting doc
2018-05-17 Updated component maps ready for board layout, adding Thumbs.db to .gitignore
2018-05-17 Updated first cut at board layout
2018-05-17 Updated to fix missing power pins for LCDs, updated DFN chips with right pinout
2018-05-17 Adding DIP library for DIP to DFN converter, Updated board layout with autorouting, hopefully v0.1 final design
2018-05-17 Added filled version with ground plane (milling?)
2018-05-23 Manufacturered board ZIP file
2018-05-28 Motor test now works on all 8 faders)
2018-05-28 Datasheet for right demux
2018-05-28 Updated for multiple faders (working, OLED won't yet due to board wrong wiring)
2018-05-28 Snagging complete on Schematic - PCB still out of date
2018-05-28 Missing file
2018-05-28 Added prototype label
2018-05-30 Fixing OLED code
2018-05-31 Removed SD_13XX submodule
2018-06-02 Rolling back RST code in library, may not be able to use it (need to demux RST)
2018-06-02 Updated to add new 74x138 for RST line (to make coding easier)
2018-06-02 Updated with new DRSTx functionality, Updated silkscreen for fader to include cut slot and screws (for use with panel cutter), Still need to modify display silkscreen, Sanitised .gitignore
2018-06-03 Adding display actual dims to datasheet JPG
2018-06-03 Removed SSD submodule
2018-06-03 Move POC tests to etc/ folder
2018-06-03 Move POC tests to etc/ folder
    Update multi-oled POC to work with RST line behind 74xx138
2018-06-03 Updated displays with silkscreen additions for cutouts, Updated PCB latest version (NOTE may need to change CAP1296 DFN to DIP adaptor depending on recent purchase / availability
2018-06-03 Adding skeleton project for Arduino Mega faderboard
    NOTE: This uses https://github.com/ladislas/Bare-Arduino-Project
2018-06-03 On second thoughts, I don't like this library
2018-06-03 Adding main file (nothing in it yet), tidying POC components
2018-06-03 Adding LoRa duplex test / example
2018-06-03 Working display initialisation code
2018-06-04 Adding silkscreen files
2018-06-04 Updated to read fader values, Added LoRa additional trials (thinking of RFM69 not the RA-02)
2018-06-07 Adding lasercut file for fader board
2018-06-10 Moving all test code to docs/ and adding Pi test code
2018-06-10 Moving main ino file to sensible place, adding memory diag code, working radio tx/rx and POC
2018-06-10 Updating PCB and schema for ProtoAdvantage DIP to DFN adapter (not great but easier than SMD on this board). Rerouting and manual edits to conform to DRC / track & pad clearance
2018-06-11 Adding boundary to Lasercut
2018-06-12 Amended library for PROTO DIP adapter to proper hole size, exported final v1.0 board for fabrication, Lasercut now complete with sides and base.
2018-06-16 Adding arduino kicad library for shield
2018-06-16 Update board connections for v1.0 board
2018-06-16 Type fix
2018-06-16 Removing unused kicad files
2018-06-16 Added SVG of v1.0 schema
2018-06-16 Adding board controller and RFM library submodule
2018-06-16 Adding libraries for Arduino and RFM, First cut at controller schematic
2018-06-16 Adding component libraries and docs for keypad and LED drivers. Still need to add TFT before complete
2018-06-17 Moving first test of rpi-rfm69 - not sure I want to use this library yet
2018-06-17 Adding submodule for pi Python X32 library and adding .swp (VIM) to .gitignore
2018-06-17 Adding etrombly (better\!) RFM69 library, first add of templatey pi code
2018-06-17 Adding retry code to avoid continual radio pounding
2018-06-17 Adding 74xx4050 datasheet
2018-06-17 Adding TFT test and initial TFT code to main file
2018-06-17 Updated to add TFT display components, and now using customer SSD1331 module to fix mixed mode problem
2018-06-17 Updated lib
2018-06-17 Adding working first steps at a receiver module
2018-06-17 Changing radio params to work properly (can probably reduce timeout now)
2018-06-17 Fixing TFT_ pinouts and rebuilding PCB
2018-06-17 Adding first autoroute - still need to check nets are correct
2018-06-21 Completed v0.1 of controller board, added PDFs for boards and datasheet for RFM radio
2018-06-23 Tidying board output file locations, corrected silkscreen for v1.0 fader board (not fabbed)
2018-06-23 Adding Inkscape doc and tidying DXF view
2018-06-23 Adding link to Google sheet
2018-06-23 Removed erroneous file
2018-07-15 Added new T-Slot version of the box
2018-08-27 Adding mac files to gitignore
2018-10-06 Changes to BAUD for tests, major update for faderboard code to work with current PCB versions (incl BSEL screw-up)
